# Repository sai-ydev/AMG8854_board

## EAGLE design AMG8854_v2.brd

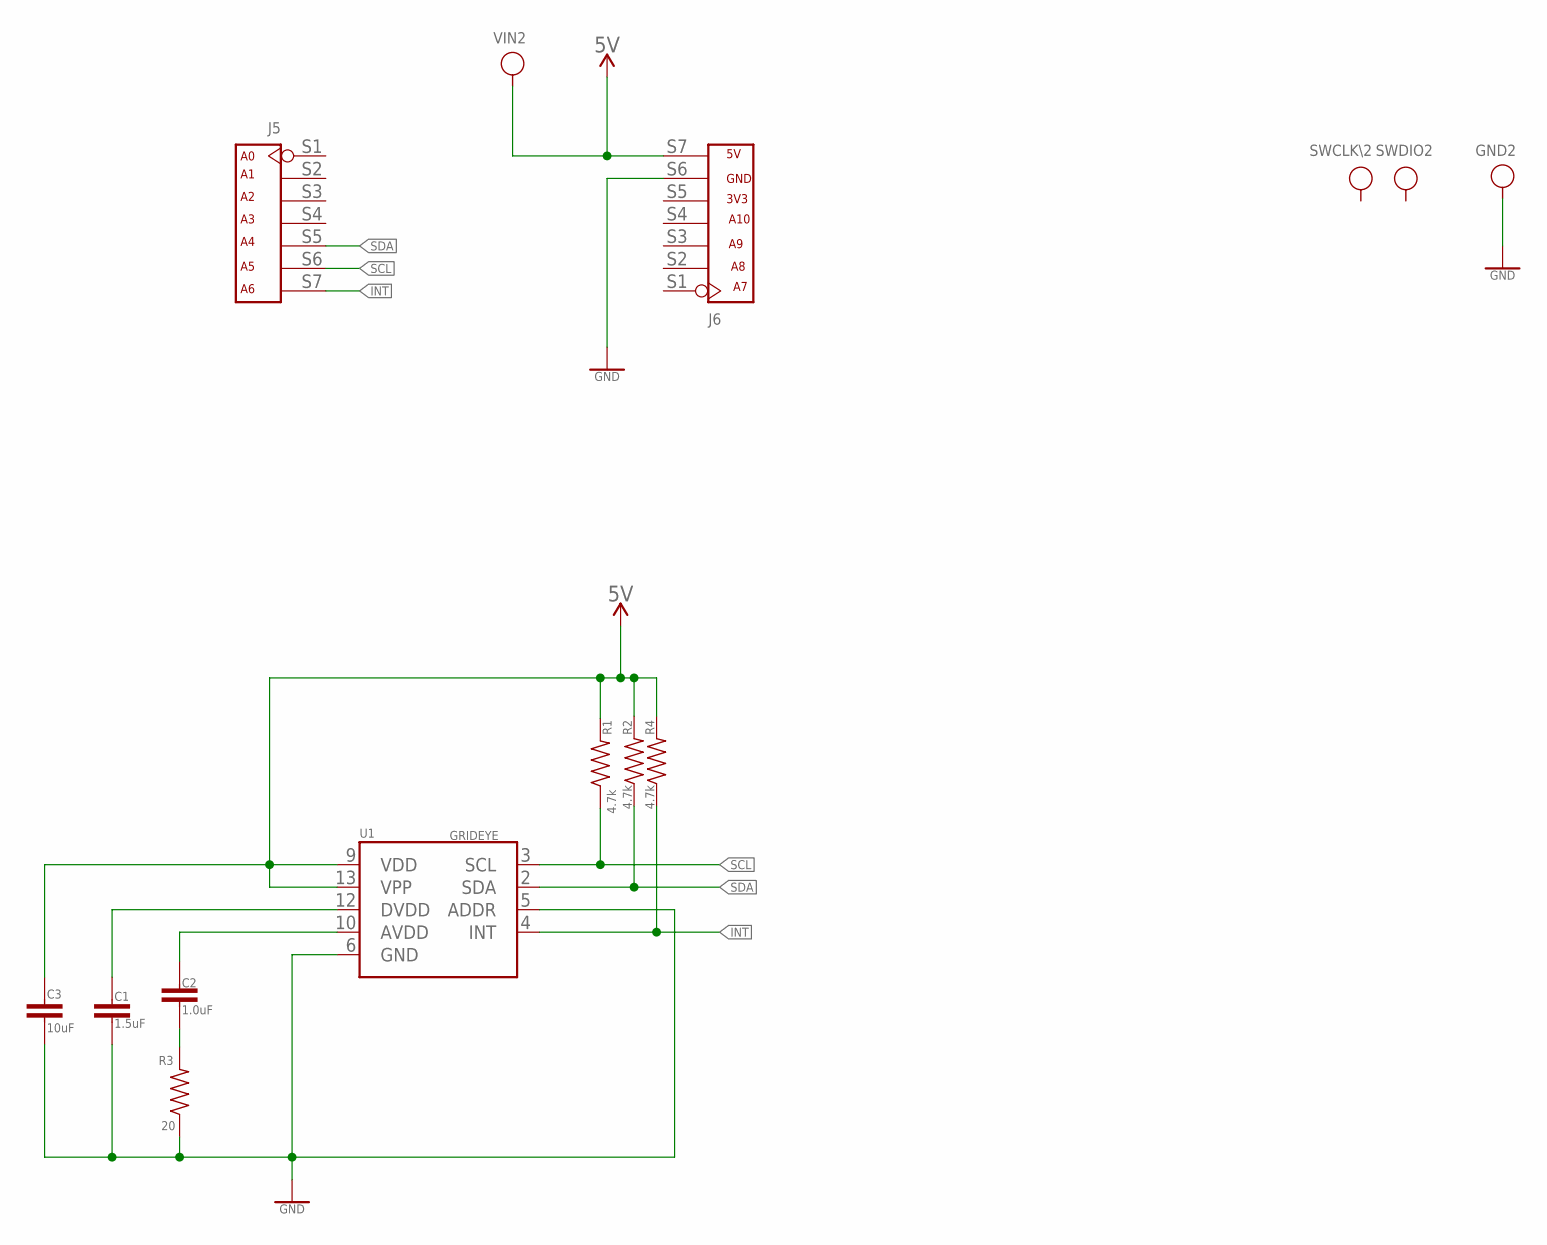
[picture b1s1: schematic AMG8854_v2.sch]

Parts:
C1: 1.5uF; 0603
C2: 1.0uF; 0603
C3: 10uF; 0603
GND2: TEST-POINT'4080'; TP-80X40MIL
J5, J6: DNP; CONNECTOR-V2
R1, R2, R4: 4.7k; 0603
R3: 20; 0603
SWCLK\2: TEST-POINT'4545'; TP-D45MIL
SWDIO2: TEST-POINT'4545'; TP-D45MIL
U1: GRIDEYE; GRIDEYE-AMG88
VIN2: TEST-POINT'4080'; TP-80X40MIL

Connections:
5V: C3.1, J6.S7 (7), R1.2, R2.2, R4.2, U1.9 (VDD), U1.13 (VPP), VIN2.1
GND: C1.2, C3.2, GND2.1, J6.S6 (6), R3.1, U1.5 (ADDR), U1.6 (GND)
INT: J5.S7 (7), R4.1, U1.4 (INT)
unnamed: C1.1, U1.12 (DVDD)
unnamed: C2.2, R3.2
unnamed: C2.1, U1.10 (AVDD)
SCL: J5.S6 (6), R1.1, U1.3 (SCL)
SDA: J5.S5 (5), R2.1, U1.2 (SDA)

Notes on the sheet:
A10
3V3
GND

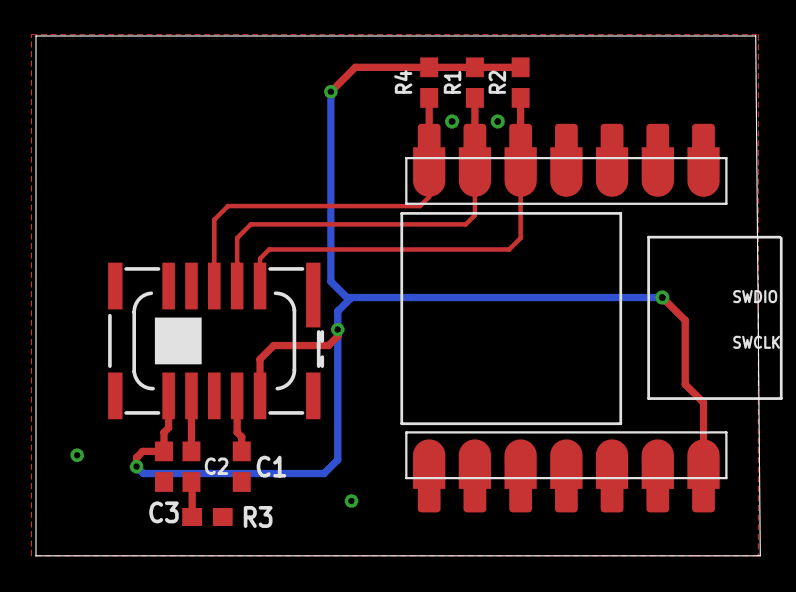
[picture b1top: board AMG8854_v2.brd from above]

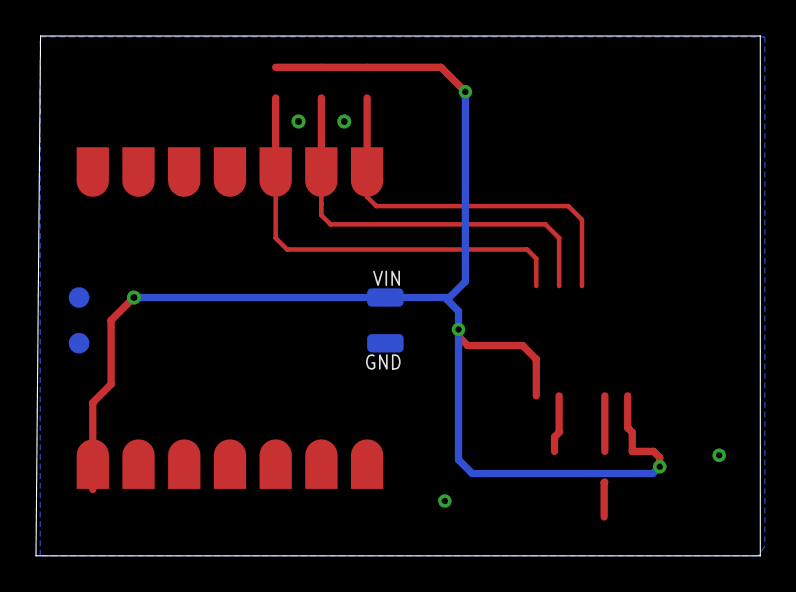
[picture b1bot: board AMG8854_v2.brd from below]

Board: 2 copper layers, 40.2 x 28.9 mm, 14 parts (4 on the bottom side), 8 nets.

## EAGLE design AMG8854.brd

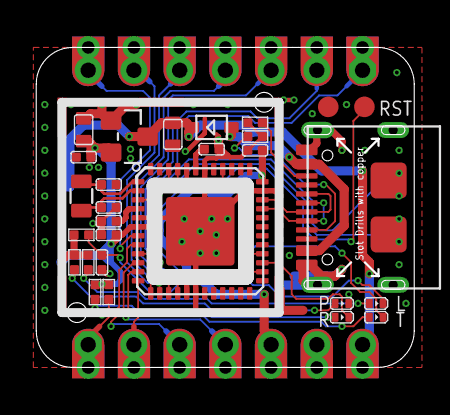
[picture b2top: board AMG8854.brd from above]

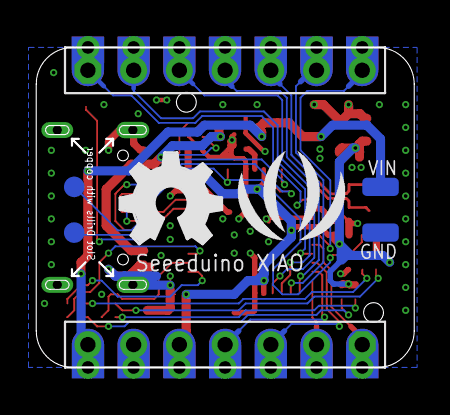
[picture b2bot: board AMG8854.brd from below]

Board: 2 copper layers, 21.0 x 17.8 mm, 37 parts (6 on the bottom side), 33 nets.

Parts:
C1, C2, C39, C41: 100nF; C0402
C5, C6: 10uF; C0603
C8, C9: 1uF; C0402
C45, C46: 12pF; C0402
D4: B0540WS-7; SOD323
GND: TP-80X40MIL
J2, J4: DNP; H7-HALF-HOLE-2.54
L: YELLOW; LED-0402
LOGO1: LOGO-OSHW-FILLX0200-NT; OSHW_FILLX200_NOTEXT
MP1: SHIELDING-COVER-12.3X11.9X0.2MM
PWR: GREEN; LED-0402
R1, R2: 5.1k; R0402
R3, R4, R6, R7: 1k; R0402
R5: 10k; R0402
RX: BLUE; LED-0402
TP2, TP3, TP4, TP5: TP-D45MIL
TX: BLUE; LED-0402
U1: XC6206P332MR; SOT-23
U2: ATSAMD21G18-QFN48; QFN48-7X7
U$3: LOGO-SEEED-BIG-SILK; SEEED-SILK-280*268MIL
USB1: USB2.0-TYPE-C
VIN: TP-80X40MIL
X1: 32.768KHz; X2-SMD-L2.0X1.2X0.55MM

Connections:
3V3: C2.2, C6.2, C39.2, C41.2, J4.5, J4.17, R3.1, R4.1, R5.1, R6.1, R7.1, U1.2, U2.6, U2.17, U2.36, U2.44
5V: C5.2, D4.-, J4.7, J4.19, U1.3, VIN.1
GND: C1.2, C2.1, C5.1, C6.1, C8.1, C9.1, C39.1, C41.1, C45.1, C46.1, GND.1, J4.6, J4.18, MP1.1, MP1.2, MP1.3, MP1.4, MP1.5, MP1.6, PWR.-, R1.2, R2.1, TP4.T, U1.1, U2.5, U2.18, U2.35, U2.42, U2.PAD, USB1.A1_B12, USB1.B1_A12, USB1.S1, USB1.S2, USB1.S3, USB1.S4, USB1.S5, USB1.S6
unnamed: R1.1, USB1.A5
unnamed: R2.2, USB1.B5
unnamed: C8.2, U2.43
unnamed: C9.2, U2.4
unnamed: L.+, R3.2
unnamed: R7.2, TX.+
unnamed: C45.2, U2.2, X1.2
unnamed: R4.2, RX.+
unnamed: C46.2, U2.1, X1.1
unnamed: PWR.+, R6.2
PA02_A0_D0: J2.1, J2.13, U2.3
PA4_A1_D1: J2.2, J2.14, U2.9
PA5_A9_D9_MISO: J4.3, J4.15, U2.10
PA6_A10_D10_MOSI: J4.4, J4.16, U2.11
PA7_A8_D8_SCK: J4.2, J4.14, U2.12
PA8_A4_D4_SDA: J2.5, J2.17, U2.13
PA9_A5_D5_SCL: J2.6, J2.18, U2.14
PA10_A2_D2: J2.3, J2.15, U2.15
PA11_A3_D3: J2.4, J2.16, U2.16
PA17_W13: L.-, U2.26
PA18_RX_LED: RX.-, U2.27
PA19_TX_LED: TX.-, U2.28
PA30_SWCLK: TP3.T, U2.45
PA31_SWDIO: TP5.T, U2.46
PB08_A6_D6_TX: J2.7, J2.19, U2.7
PB09_A7_D7_RX: J4.1, J4.13, U2.8
RESET: C1.1, R5.2, TP2.T, U2.40
USB_D+: U2.34, USB1.A6, USB1.B6
USB_D-: U2.33, USB1.A7, USB1.B7
VBUS: D4.+, USB1.A4_B9, USB1.B4_A9

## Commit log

2020-07-05 Check-in

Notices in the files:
parts and their libraries:
SparkFun-Resistors: Licensing: Creative Commons ShareAlike 4.0 International - https://creativecommons.org/licenses/by-sa/4.0
